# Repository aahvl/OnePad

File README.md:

---

# OnePad

A special OneKey macropad, featuring just One Key, Backlighting for the key, a rotary encoder, 6 RGB LEDs, and a special engraved OneKey Case!
This can be customized and programmed with Cherry MX Hotswap keys, a custom knob for the rotary encoder, and firmware wise, QMK!

You can view a 3D Model (Assembly 1) of the casing [here!](https://cad.onshape.com/documents/d49002deca5d7f8962891b9d/w/8e326d7ba50aee91844e6f32/e/19b3f74cfa64233b2a067eb7?renderMode=0&uiState=6a523a298b3d0d21d2dd9cd4)

## The Highlights
- 1 Hotswappable Cherry MX mechanical switch
- EC11E Rotary Encoder
- 1x SK6812MINI-E LEDs for backlights!
- 6x SK6812MINI LEDs for nice lighting!
- Connect via USB-C

## More photos!

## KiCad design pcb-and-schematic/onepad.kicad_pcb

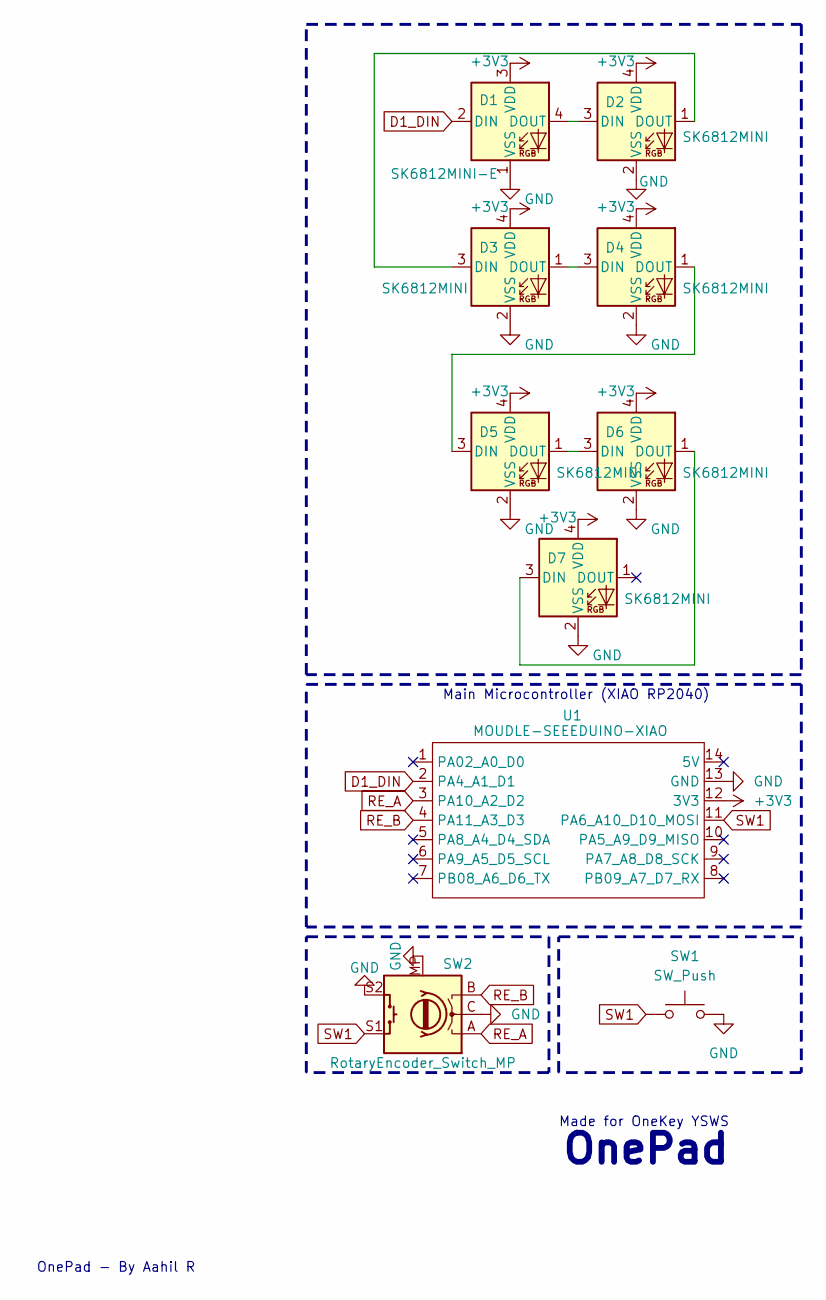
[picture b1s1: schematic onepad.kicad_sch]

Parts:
D1: SK6812MINI-E; LED_SK6812MINI-E_3.2x2.8mm_P1.5mm_ReverseMount
D2, D3, D4, D5, D6, D7: SK6812MINI; LED_SK6812MINI_PLCC4_3.5x3.5mm_P1.75mm
SW1: SW_Push; SW_MX_HS_CPG151101S11_1u
SW2: RotaryEncoder_Switch_MP; RotaryEncoder_Alps_EC11E-Switch_Vertical_H20mm
U1: MOUDLE-SEEEDUINO-XIAO; XIAO-Generic-Hybrid-14P-2.54-21X17.8MM

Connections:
+3V3: D1.3 (VDD), D2.4 (VDD), D3.4 (VDD), D4.4 (VDD), D5.4 (VDD), D6.4 (VDD), D7.4 (VDD), U1.12 (3V3)
D1_DIN: D1.2 (DIN), U1.2 (PA4_A1_D1)
GND: D1.1 (VSS), D2.2 (VSS), D3.2 (VSS), D4.2 (VSS), D5.2 (VSS), D6.2 (VSS), D7.2 (VSS), SW1.2, SW2.C, SW2.MP, SW2.S2, U1.13 (GND)
unnamed: D1.4 (DOUT), D2.3 (DIN)
unnamed: D2.1 (DOUT), D3.3 (DIN)
unnamed: D3.1 (DOUT), D4.3 (DIN)
unnamed: D4.1 (DOUT), D5.3 (DIN)
unnamed: D5.1 (DOUT), D6.3 (DIN)
unnamed: D6.1 (DOUT), D7.3 (DIN)
RE_A: SW2.A, U1.3 (PA10_A2_D2)
RE_B: SW2.B, U1.4 (PA11_A3_D3)
SW1: SW1.1, SW2.S1, U1.11 (PA6_A10_D10_MOSI)

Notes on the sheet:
Main Microcontroller (XIAO RP2040)
OnePad - By Aahil R
Made for OneKey YSWS
OnePad

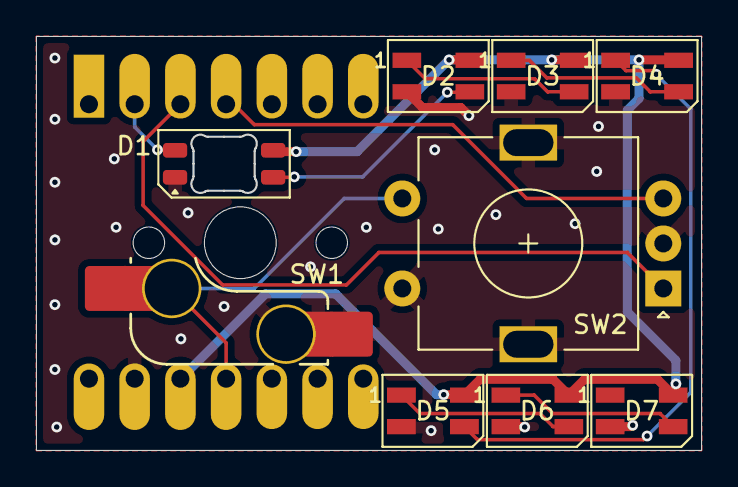
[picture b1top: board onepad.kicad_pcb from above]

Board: 2 copper layers, 37.0 x 23.0 mm, 10 parts (1 on the bottom side), 12 nets.

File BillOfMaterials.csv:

"Id";"Designator";"Footprint";"Quantity";"Designation";"Supplier and ref";
1;"D1";"SK6812MINI-E_DOO";1;"SK6812MINI-E";"LCSC: C5149201";
2;"D2,D3,D4,D5,D6,D7";"SK6812MINI";6;"SK6812MINI";"LCSC: C5149201";
3;"SW2";"RotaryEncoder_Alps_EC11E-Switch_Vertical_H20mm";1;"RotaryEncoder_Switch_MP";"LCSC: C2682947";
4;"SW1";"SW_MX_HS_CPG151101S11_1u";1;"SW_Push";"LCSC: C5156480";
5;"U1";"XIAO-Generic-Hybrid-14P-2.54-21X17.8MM";1;"MODULE-SEEEDUINO-XIAO";"LCSC: C2924195";
